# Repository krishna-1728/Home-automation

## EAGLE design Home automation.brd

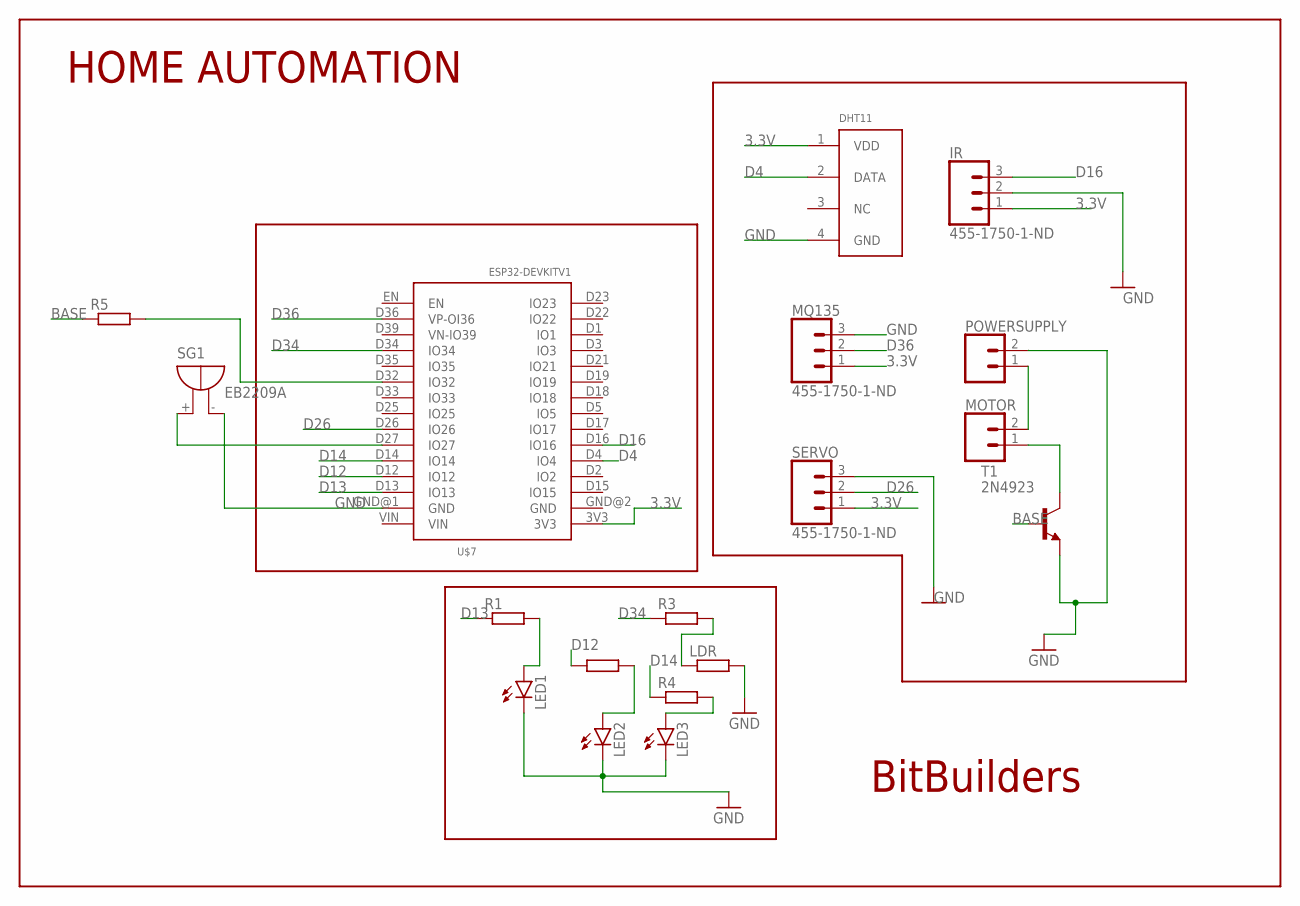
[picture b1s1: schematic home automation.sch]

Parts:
DHT11: DHT11
IR: 455-1750-1-ND; 1X03
LDR: R-EU_0204/7; 0204/7
LED1, LED2, LED3: LED5MM
MOTOR: CONN_02; 1X02
MQ135: 455-1750-1-ND; 1X03
POWERSUPPLY: CONN_02; 1X02
R1, R2, R3: R-EU_0204/5; 0204/5
R4, R5: R-EU_0204/7; 0204/7
SERVO: 455-1750-1-ND; 1X03
SG1: EB2209A
T1: 2N4923; TO126
U$7: ESP32DEVKITV1; ESP32-DEVKITV1

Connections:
3.3V: DHT11.1 (VDD), IR.1, MQ135.1, SERVO.1, U$7.3V3
BASE: R5.1, T1.3 (B)
D4: DHT11.2 (DATA), U$7.D4 (IO4)
D12: R2.1, U$7.D12 (IO12)
D13: R1.1, U$7.D13 (IO13)
D14: R4.1, U$7.D14 (IO14)
D16: IR.3, U$7.D16 (IO16)
D26: SERVO.2, U$7.D26 (IO26)
D34: R3.1, U$7.D34 (IO34)
D36: MQ135.2, U$7.D36 (VP-OI36)
GND: DHT11.4 (GND), IR.2, LDR.2, LED1.K (C), LED2.K (C), LED3.K (C), MQ135.3, POWERSUPPLY.2, SERVO.3, SG1.-, T1.1 (E), U$7.GND@1 (GND)
unnamed: SG1.+, U$7.D27 (IO27)
unnamed: MOTOR.1, T1.2 (C)
unnamed: LED1.A, R1.2
unnamed: LED2.A, R2.2
unnamed: LED3.A, R4.2
unnamed: LDR.1, R3.2
unnamed: MOTOR.2, POWERSUPPLY.1
unnamed: R5.2, U$7.D32 (IO32)

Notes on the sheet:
HOME AUTOMATION
BitBuilders

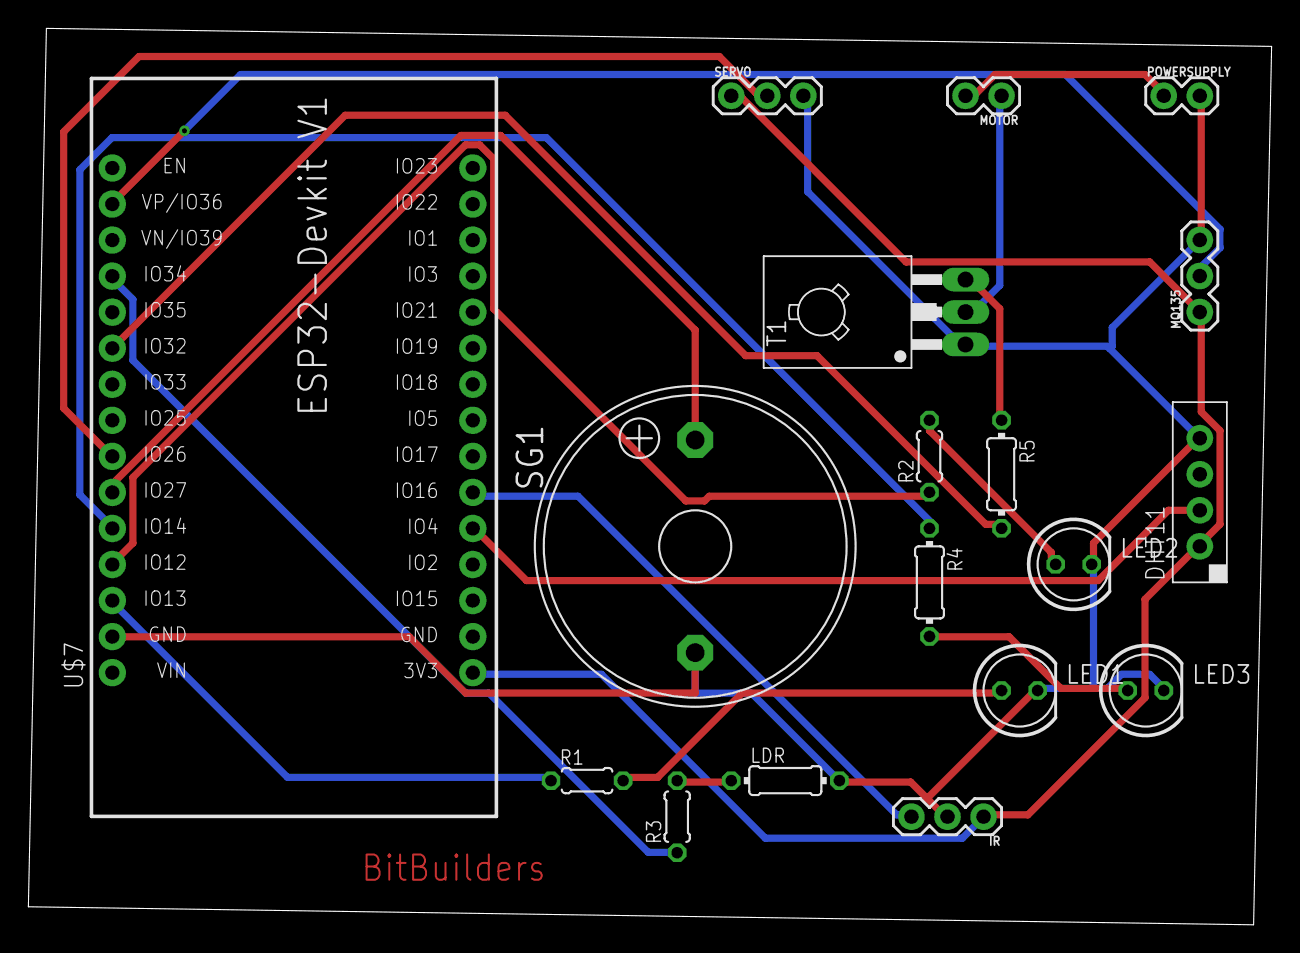
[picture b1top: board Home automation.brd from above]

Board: 2 copper layers, 87.6 x 63.2 mm, 18 parts (0 on the bottom side), 19 nets.

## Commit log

2025-03-30 Create PCB DESIGN
2025-03-30 Create jj

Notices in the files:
parts and their libraries:
SparkFun-Connectors: Licensing: Creative Commons ShareAlike 4.0 International - https://creativecommons.org/licenses/by-sa/4.0
